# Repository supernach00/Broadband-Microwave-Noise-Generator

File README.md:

# LEEME

## Contenido.
- **PDFs:** Paper, hojas de datos, esquemático.
- **SPICE:** Simulaciones en spice. Antes de correrlas instalate las librerias (lib), te explico más abajo cómo.
- **PCB:** Diseño de la pcb en kicad.

## Instalación de librerias de spice.
1. Copiá el archivo **lib** en **C:\Users\ ____ \AppData\Local\LTspice\lib**. Reemplazalo pero igual fijate de guardar en algún lado el **lib** que ya existe por si hacés cagada. Fijate que la ruta puede ser un poco distinta también pero no debe ser muy distinta.
2. Listo.

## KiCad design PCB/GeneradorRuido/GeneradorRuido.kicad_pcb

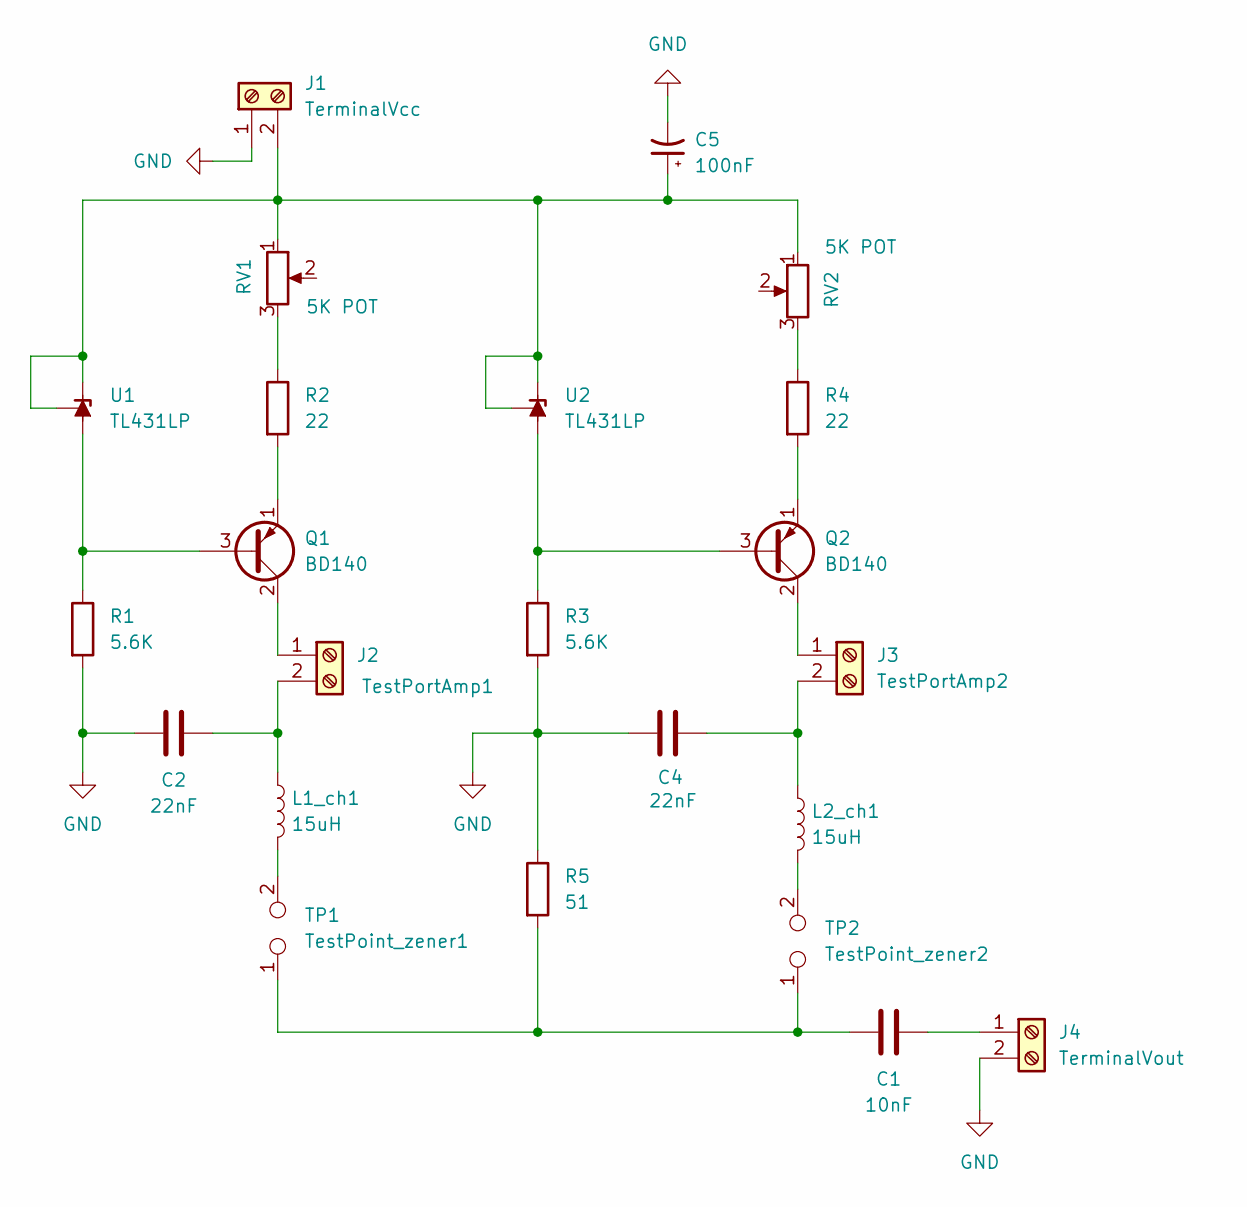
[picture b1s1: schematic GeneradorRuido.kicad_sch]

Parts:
C1: 10nF; C_Disc_D6.0mm_W2.5mm_P5.00mm
C2, C4: 22nF; C_Disc_D6.0mm_W2.5mm_P5.00mm
C5: 100nF; CP_Radial_D8.0mm_P5.00mm
J1: TerminalVcc; TerminalBlock_bornier-2_P5.08mm
J2: TestPortAmp1; TerminalBlock_bornier-2_P5.08mm
J3: TestPortAmp2; TerminalBlock_bornier-2_P5.08mm
J4: TerminalVout; TerminalBlock_bornier-2_P5.08mm
L1_ch1, L2_ch1: 15uH; L_Axial_L6.6mm_D2.7mm_P10.16mm_Horizontal_Vishay_IM-2
Q1, Q2: BD140; TO-126-3_Vertical
R1, R3: 5.6K; R_Axial_DIN0207_L6.3mm_D2.5mm_P10.16mm_Horizontal
R2, R4: 22; R_Axial_DIN0207_L6.3mm_D2.5mm_P10.16mm_Horizontal
R5: 51; R_Axial_DIN0207_L6.3mm_D2.5mm_P10.16mm_Horizontal
RV1, RV2: 5K POT; Potentiometer_Bourns_3266W_Vertical
TP1: TestPoint_zener1; D_DO-35_SOD27_P12.70mm_Horizontal
TP2: TestPoint_zener2; D_DO-35_SOD27_P12.70mm_Horizontal
U1, U2: TL431LP; TO-92_Inline

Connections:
GND: C2.1, C4.1, C5.2, J1.1, J4.2, R1.2, R3.2, R5.1
unnamed: C1.1, R5.2, TP1.1, TP2.1
unnamed: C5.1, J1.2, RV1.1, RV2.1, U1.1 (REF), U1.3 (K), U2.1 (REF), U2.3 (K)
unnamed: J2.1, Q1.2 (C)
unnamed: C2.2, J2.2, L1_ch1.1
unnamed: J3.1, Q2.2 (C)
unnamed: C4.2, J3.2, L2_ch1.1
unnamed: C1.2, J4.1
unnamed: L1_ch1.2, TP1.2
unnamed: L2_ch1.2, TP2.2
unnamed: Q1.3 (B), R1.1, U1.2 (A)
unnamed: Q1.1 (E), R2.2
unnamed: Q2.3 (B), R3.1, U2.2 (A)
unnamed: Q2.1 (E), R4.2
unnamed: R2.1, RV1.3
unnamed: R4.1, RV2.3

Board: 2 copper layers, 23 parts (0 on the bottom side), 16 nets, no tracks yet.

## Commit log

2025-09-27 primer commit
2025-10-02 ordenar el readme
2025-10-04 Diseñar esquematico y pcb en kicad. Faltan conexiones de pcb
